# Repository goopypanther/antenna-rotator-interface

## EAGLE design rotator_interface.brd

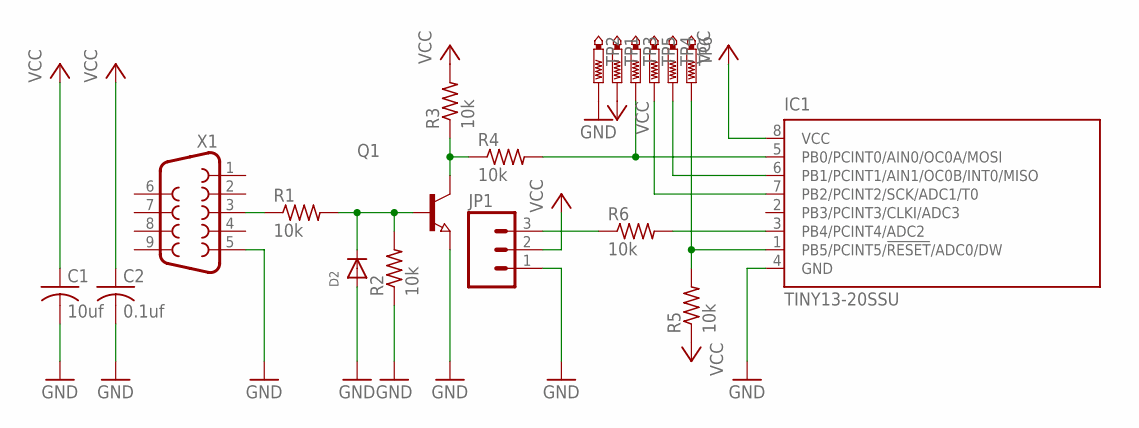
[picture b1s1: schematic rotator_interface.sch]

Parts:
C1: 10uf; C1206
C2: 0.1uf; C1206
D2: DIODESOD-123; SOD-123
IC1: TINY13-20SSU; 8S1
JP1: M03PTH; 1X03
Q1: NPN-TRANSISTOR_SOT23; SOT23
R1, R2, R3, R4, R5, R6: 10k; R1206
TP1, TP2, TP3, TP4, TP5, TP6: PTR1B1,27; B1,27
X1: DB9FEMALE; DB9

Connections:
GND: C1.2, C2.2, D2.A, IC1.4 (GND), JP1.1, Q1.2 (E), R2.1, TP2.TP, X1.5
unnamed: Q1.3 (C), R3.1, R4.1
unnamed: D2.C, Q1.1 (B), R1.2, R2.2
unnamed: R1.1, X1.3
unnamed: IC1.5 (PB0/PCINT0/AIN0/OC0A/MOSI), R4.2, TP3.TP
unnamed: IC1.1 (PB5/PCINT5/!RESET!/ADC0/DW), R5.2, TP6.TP
unnamed: IC1.6 (PB1/PCINT1/AIN1/OC0B/INT0/MISO), TP4.TP
unnamed: IC1.7 (PB2/PCINT2/SCK/ADC1/T0), TP5.TP
unnamed: IC1.3 (PB4/PCINT4/ADC2), R6.2
unnamed: JP1.3, R6.1
VCC: C1.1, C2.1, IC1.8 (VCC), JP1.2, R3.2, R5.1, TP1.TP

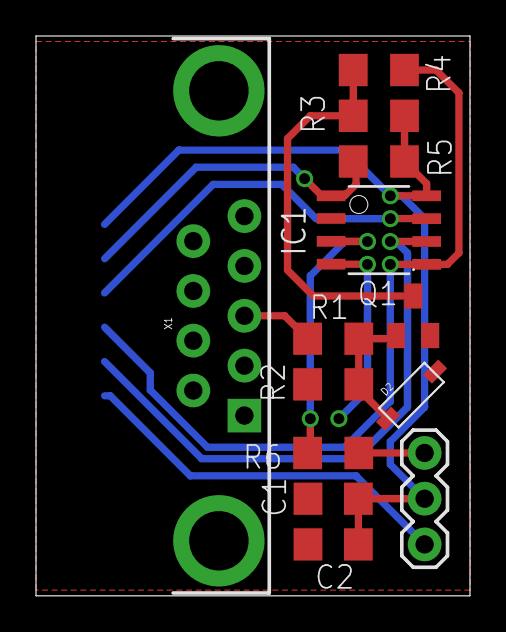
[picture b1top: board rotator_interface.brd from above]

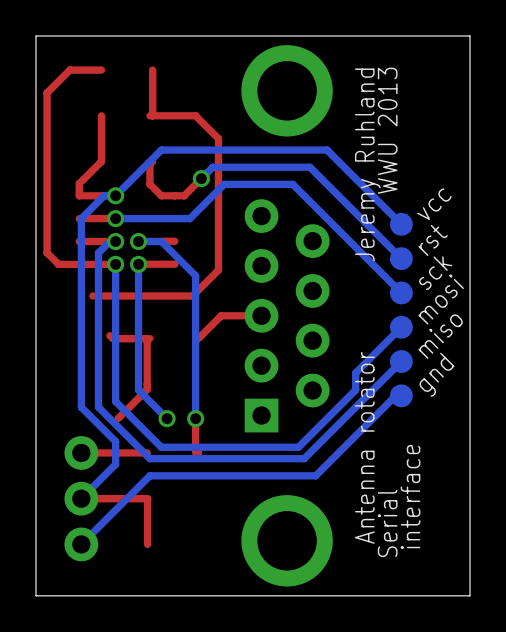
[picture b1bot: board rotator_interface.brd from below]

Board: 2 copper layers, 24.1 x 31.1 mm, 19 parts (6 on the bottom side), 11 nets.

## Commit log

2013-03-25 Moving finished design to new working directory.
2013-09-30 added firmware

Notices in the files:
parts and their libraries:
sparkfun: Licensing: CC v3.0 Share-Alike You are welcome to use this library for commercial purposes.
